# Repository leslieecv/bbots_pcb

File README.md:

# PCB Battlebots base

Este repositorio contiene las diferentes versiones de placa base, diseñadas para el curso [Battlebots](https://github.com/Battlebots-UChile) de la FCFM Uchile.
Fueron desarrolladas usando EAGLE y se complementa con el diseño

- pcbv1: utiliza Arduino UNO (funcional). Otros detalles disponibles en [Battlebot-base-testing](https://github.com/uwulises/Battlebot-base-testing).
- pcbv2: utiliza NodeMCU Amica V2 (ESP8266) y opcionalmente puede usar un Módulo Wifi ESP8266 ESP-07 (incompleta).
- pcbv3: utiliza solamente NodeMCU Amica V2 (ESP8266) (funcional). Diseño mecánico disponible en [MobileBase_ESP8266](https://github.com/uwulises/MobileBase_ESP8266).

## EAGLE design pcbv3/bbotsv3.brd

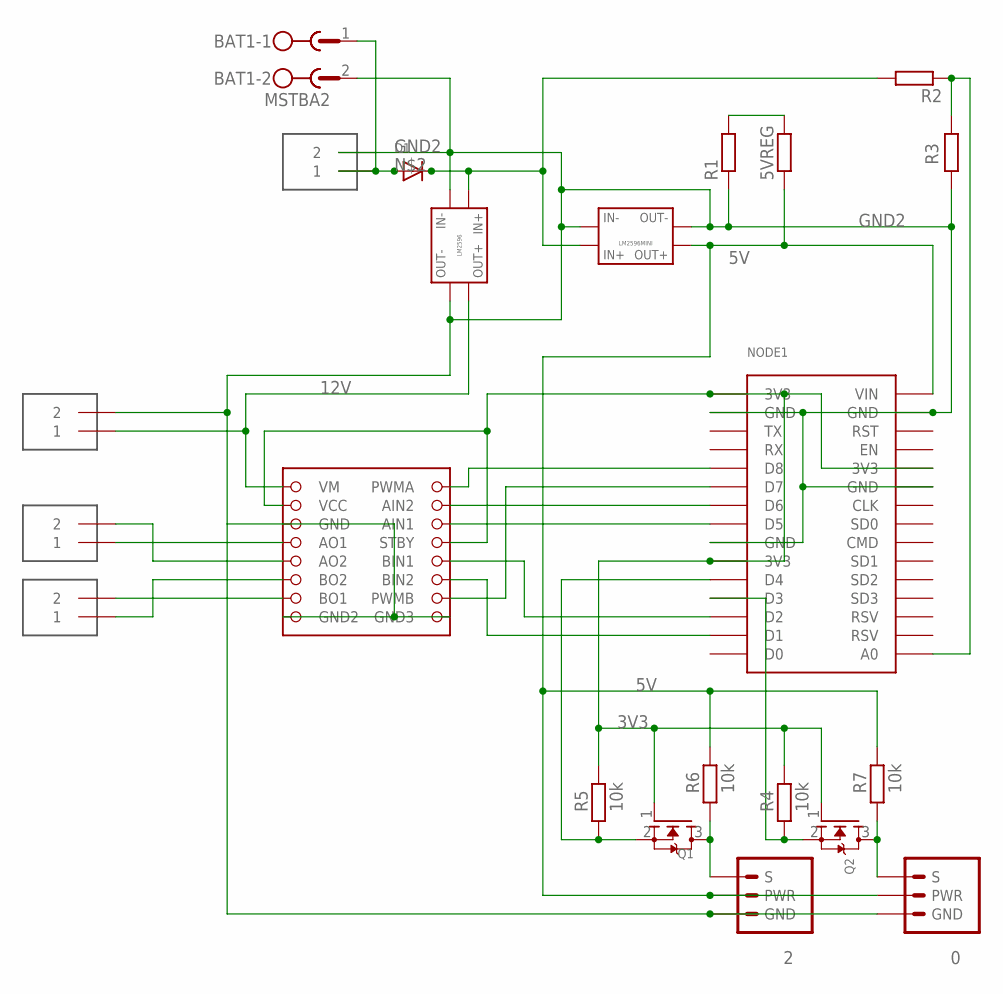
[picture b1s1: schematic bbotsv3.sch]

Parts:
0, 2: BB-PIN3BB-PIN3; 1X03
5VREG: BB-R0805; R0805
ARMA, ARMA1, ARMA2, ARMA3: TERMINAL_2P; KF301-2P
BAT1: MSTBA2
D1: DIODEDO-1N4148; DO-1N4148
NODE1: NODEMCU_ESP8266
Q1, Q2: MOSFET-NWAVE; SOT23-W
R1: 100; R1206
R2, R4, R5, R6, R7: 10k; R1206
R3: 1k; R1206
U$1: BB-LM2596
U$2: BB-TB6612
U$3: BB-LM2596MINILM2596MINIV2; LM2596MINIV2

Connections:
3V3: NODE1.3V3@1 (3V3), NODE1.3V3@2 (3V3), NODE1.3V3@3 (3V3), Q1.1 (G), Q2.1 (G), R4.2, R5.2, U$2.STBY, U$2.VCC
5V: 0.P (PWR), 2.P (PWR), 5VREG.1, NODE1.VIN, R6.2, R7.2, U$3.OUT+
11.1: D1.C, R2.2, U$1.IN+, U$3.IN+
12V: ARMA.1, U$1.OUT+, U$2.VM
GND2: 0.GND, 2.GND, ARMA.2, ARMA3.2, BAT1.2, NODE1.GND@1 (GND), NODE1.GND@2 (GND), NODE1.GND@3 (GND), NODE1.GND@4 (GND), R1.1, R3.2, U$1.IN-, U$1.OUT-, U$2.GND, U$2.GND2, U$2.GND3, U$3.IN-, U$3.OUT-
unnamed: NODE1.A0, R2.1, R3.1
unnamed: ARMA3.1, BAT1.1, D1.A
unnamed: 5VREG.2, R1.2
unnamed: NODE1.D8, U$2.PWMA
unnamed: NODE1.D7, U$2.PWMB
unnamed: ARMA2.1, U$2.BO2
unnamed: NODE1.D6, U$2.AI2 (AIN2)
unnamed: NODE1.D5, U$2.AI1 (AIN1)
unnamed: NODE1.D2, U$2.BI1 (BIN1)
unnamed: NODE1.D1, U$2.BI2 (BIN2)
unnamed: 2.S, Q1.3 (D), R6.1
unnamed: NODE1.D3, Q2.2 (S), R4.1
unnamed: ARMA1.2, U$2.AO2
unnamed: ARMA1.1, U$2.AO1
unnamed: ARMA2.2, U$2.BO1
unnamed: 0.S, Q2.3 (D), R7.1
unnamed: NODE1.D4, Q1.2 (S), R5.1

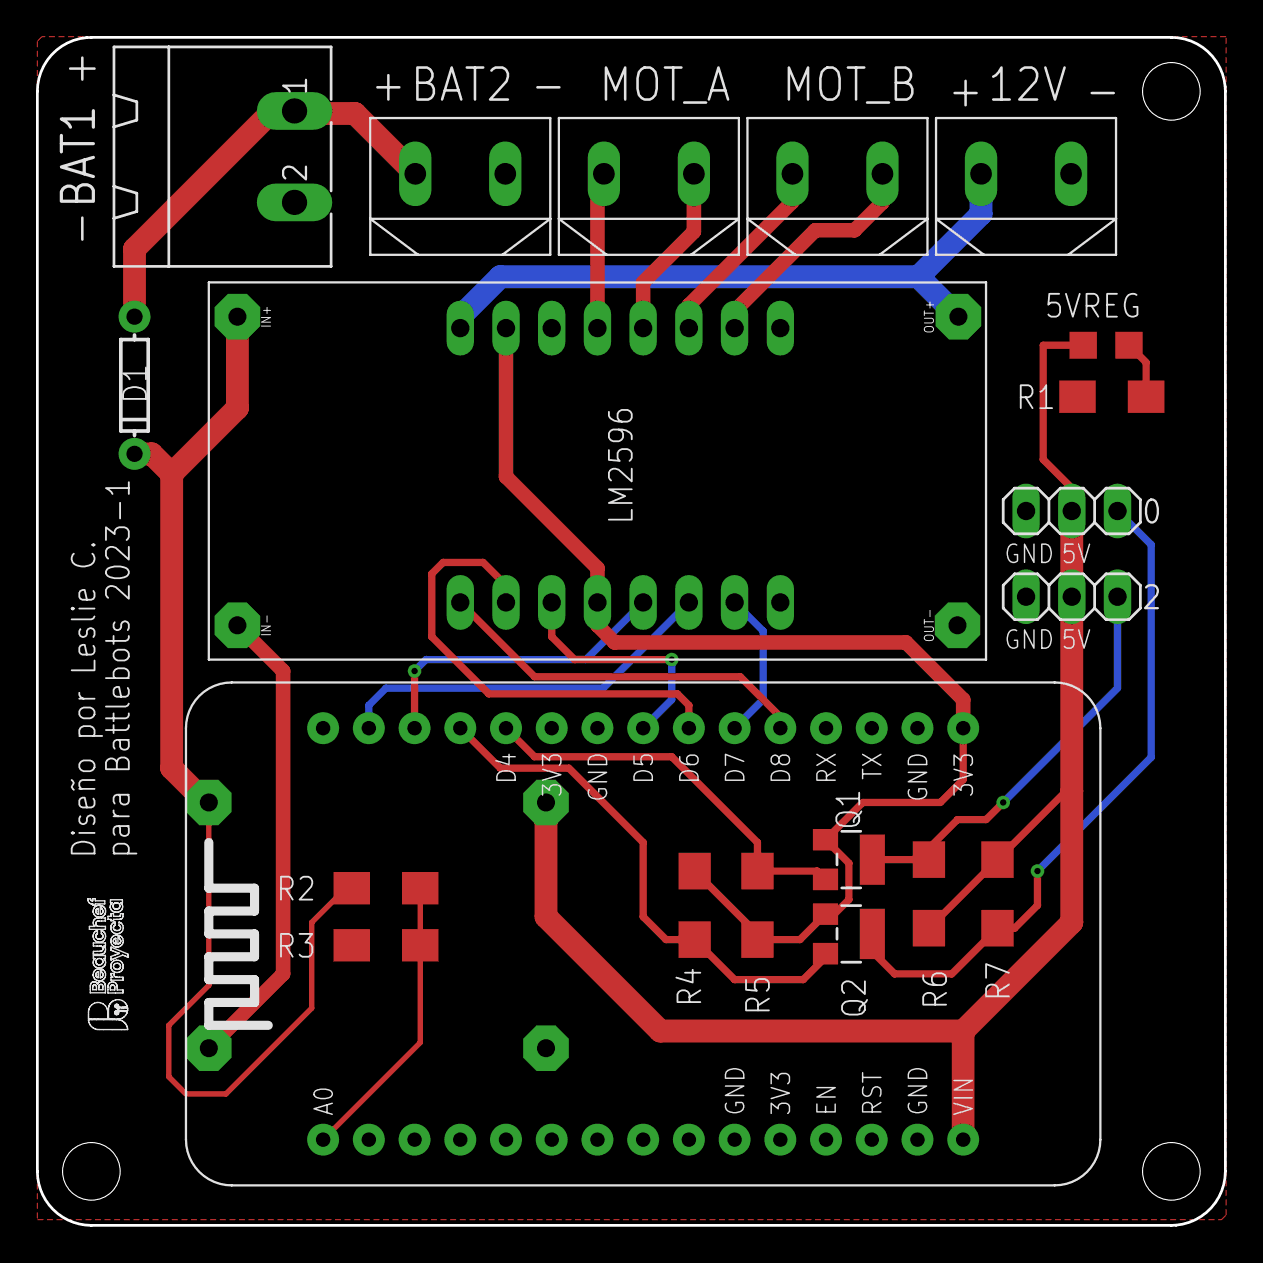
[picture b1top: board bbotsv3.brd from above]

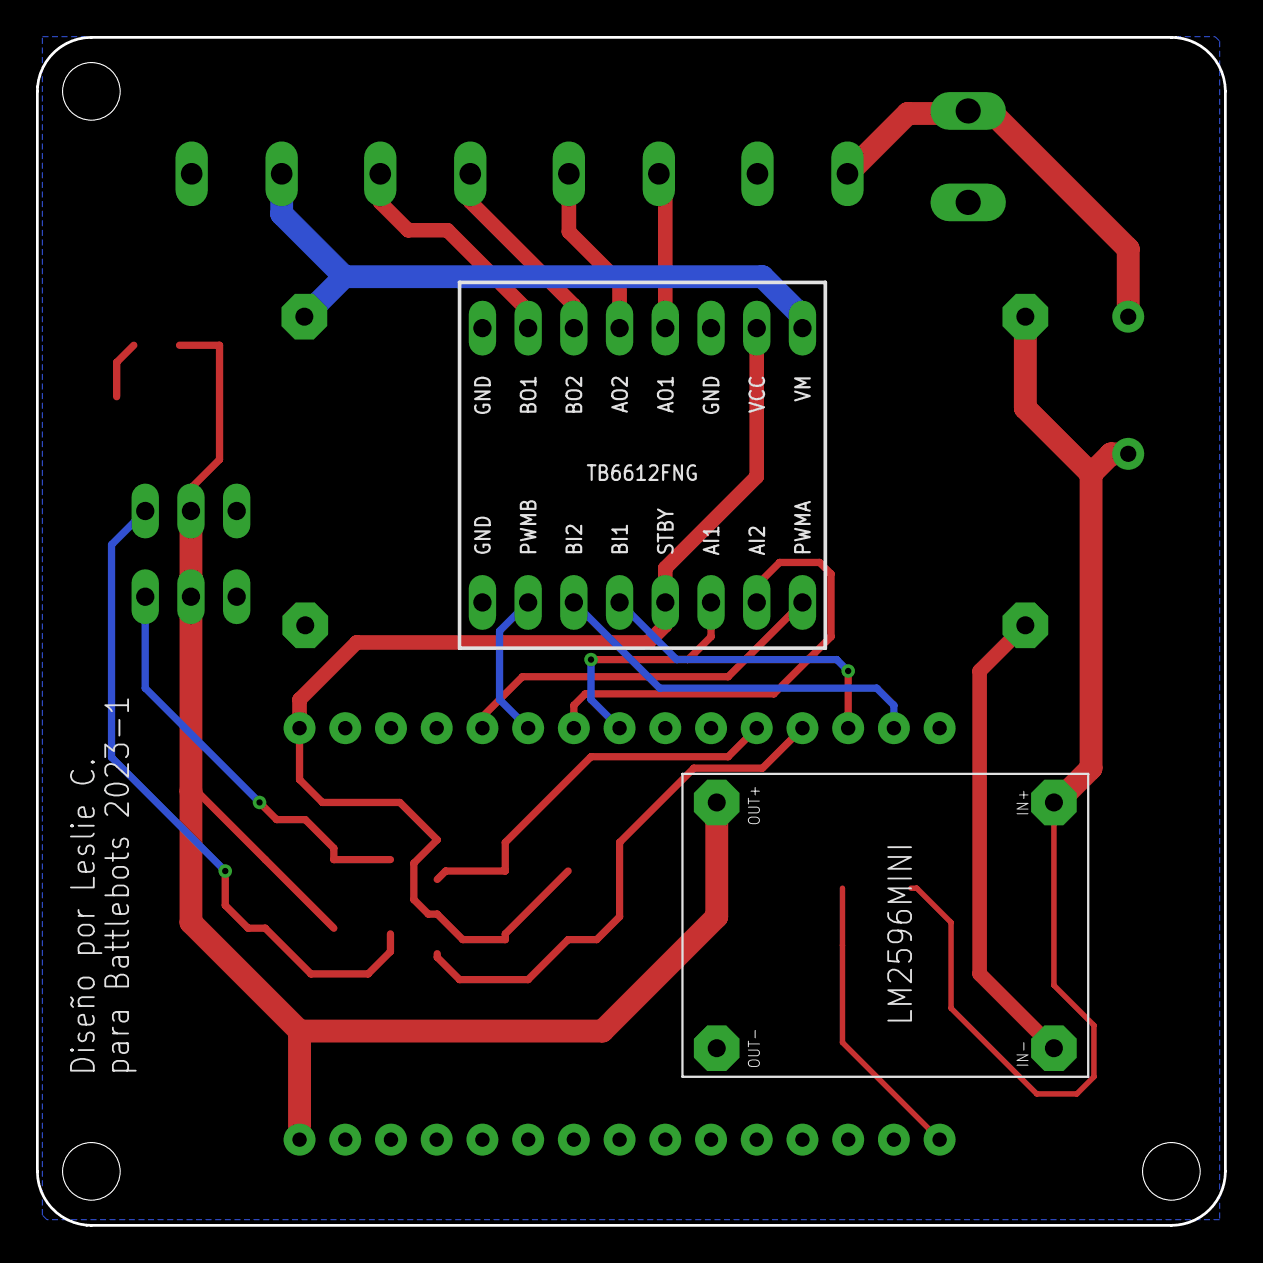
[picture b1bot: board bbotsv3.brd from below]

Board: 2 copper layers, 66.0 x 66.0 mm, 22 parts (2 on the bottom side), 22 nets.

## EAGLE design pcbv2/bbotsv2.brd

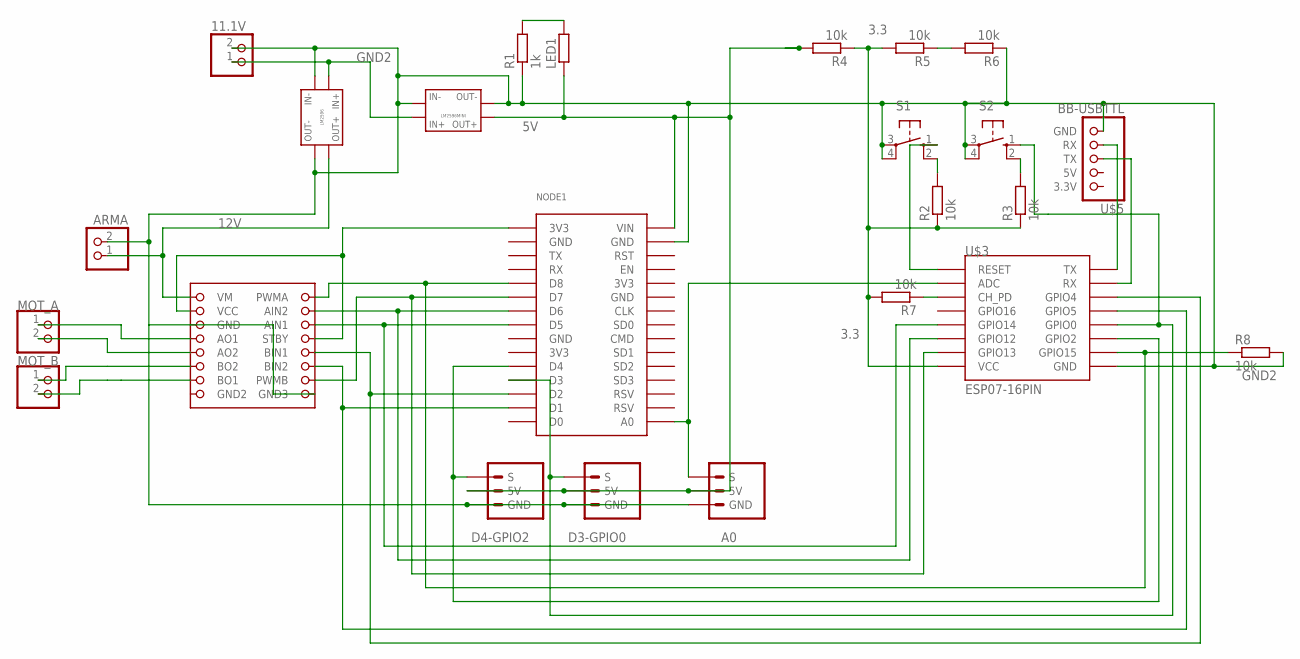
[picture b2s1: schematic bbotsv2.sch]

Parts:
11.1V: JST_2PIN-THM; JST-PH-2-THM
A0: BB-PIN3
ARMA: JST_2PIN-THM; JST-PH-2-THM
D3-GPIO0, D4-GPIO2: BB-PIN3
LED1: BB-RESM0805; M0805
MOT_A: JST_2PIN-THM; JST-PH-2-THM
MOT_B: JST_2PIN-THM; JST-PH-2-THM
NODE1: NODEMCU_ESP8266
R1: 1k; M0805
R2, R3, R4, R5, R6, R7, R8: 10k; M0805
S1, S2: 10-XX; B3F-10XX
U$1: BB-LM2596
U$2: BB-TB6612
U$3: ESP07-16PIN
U$4: BB-LM2596MINI
U$5: BB-USBTTL; 1X05

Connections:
3.3: R2.1, R3.1, R4.1, R5.2, R7.2, U$3.VCC
3V3: NODE1.3V3@2 (3V3), NODE1.3V3@3 (3V3)
5V: A0.2 (5V), D3-GPIO0.2 (5V), D4-GPIO2.2 (5V), LED1.1, NODE1.VIN, R4.2, U$4.OUT+
11.1: 11.1V.1 (2), U$1.IN+, U$4.IN+
12V: ARMA.1 (2), U$1.OUT+, U$2.VM
GND: NODE1.GND@1 (GND), NODE1.GND@2 (GND), NODE1.GND@3 (GND)
GND2: 11.1V.2 (1), A0.1 (GND), ARMA.2 (1), D3-GPIO0.1 (GND), D4-GPIO2.1 (GND), NODE1.GND@4 (GND), R1.1, R6.1, R8.2, S1.3, S1.4 (P1), S2.3, S2.4 (P1), U$1.IN-, U$1.OUT-, U$2.GND, U$2.GND3, U$3.GND, U$4.IN-, U$4.OUT-, U$5.GND; also elsewhere on the board
unnamed: LED1.2, R1.2
unnamed: NODE1.D8, R8.1, U$2.PWMA, U$3.GPIO15
unnamed: NODE1.D7, U$2.PWMB, U$3.GPIO13
unnamed: NODE1.D6, U$2.AI2 (AIN2), U$3.GPIO12
unnamed: NODE1.D5, U$2.AI1 (AIN1), U$3.GPIO14
unnamed: NODE1.D2, U$2.BI1 (BIN1), U$3.GPIO4
unnamed: NODE1.D1, U$2.BI2 (BIN2), U$3.GPIO5
unnamed: D4-GPIO2.3 (S), NODE1.D4, U$3.GPIO2
unnamed: MOT_A.2 (1), U$2.AO2
unnamed: MOT_A.1 (2), U$2.AO1
unnamed: MOT_B.1 (2), U$2.BO2
unnamed: MOT_B.2 (1), U$2.BO1
unnamed: NODE1.3V3@1 (3V3), U$2.STBY, U$2.VCC
unnamed 20: D3-GPIO0.3 (S), NODE1.D3, S2.1 (S), U$3.GPIO0; also elsewhere on the board
unnamed: U$3.TX, U$5.RX
unnamed: U$3.RX, U$5.TX
unnamed: A0.3 (S), NODE1.A0, U$3.ADC
unnamed 24: R2.2, S1.2 (S1); also elsewhere on the board
unnamed 25: R3.2, S2.2 (S1); also elsewhere on the board
unnamed: R5.1, R6.2
unnamed 27: S1.1 (S), U$3.REST (RESET); also elsewhere on the board
unnamed: R7.1, U$3.CH_PD

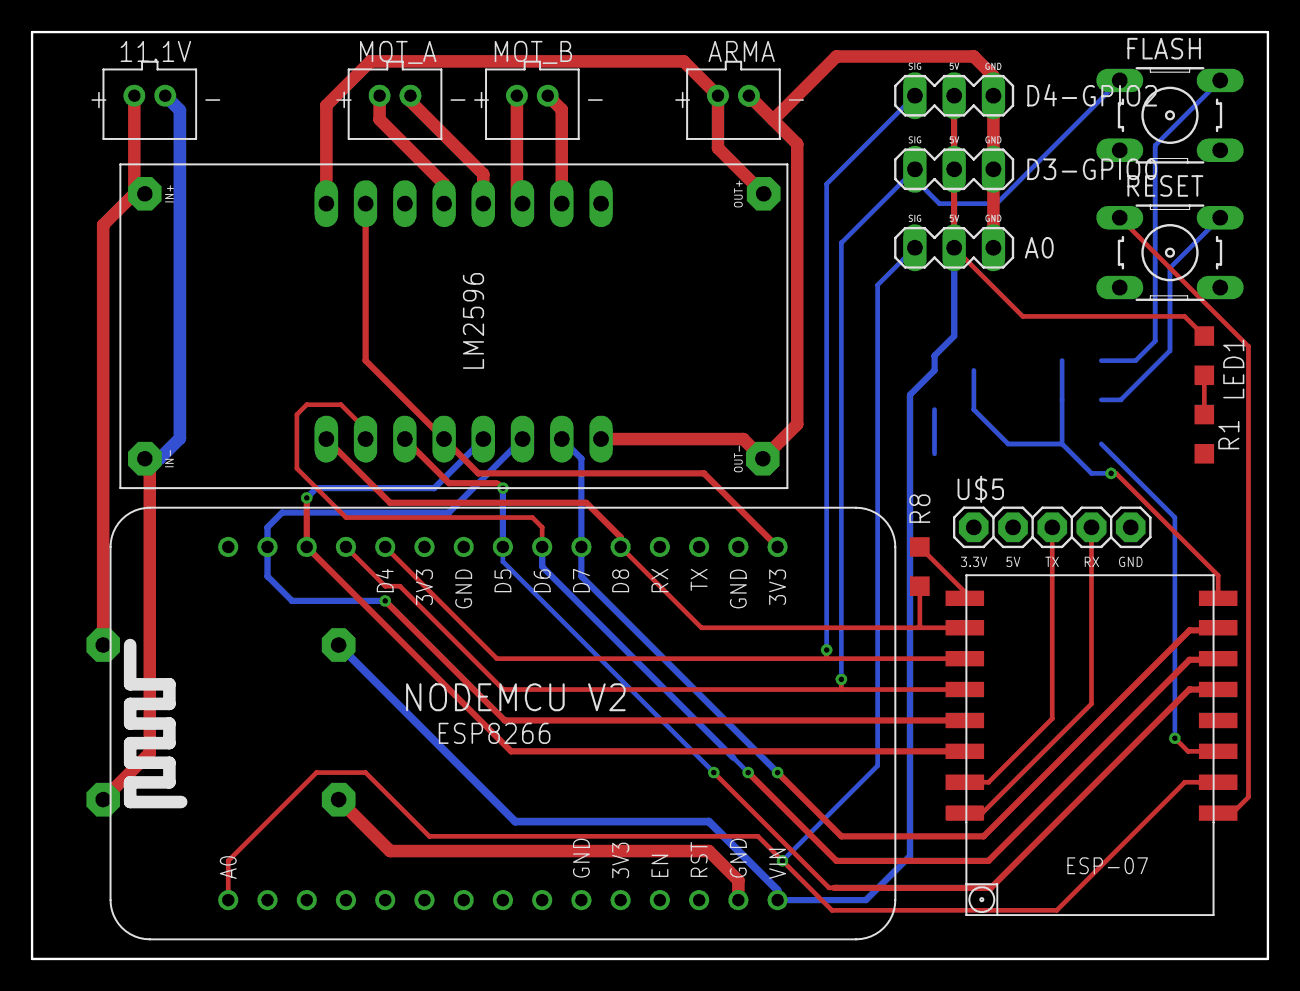
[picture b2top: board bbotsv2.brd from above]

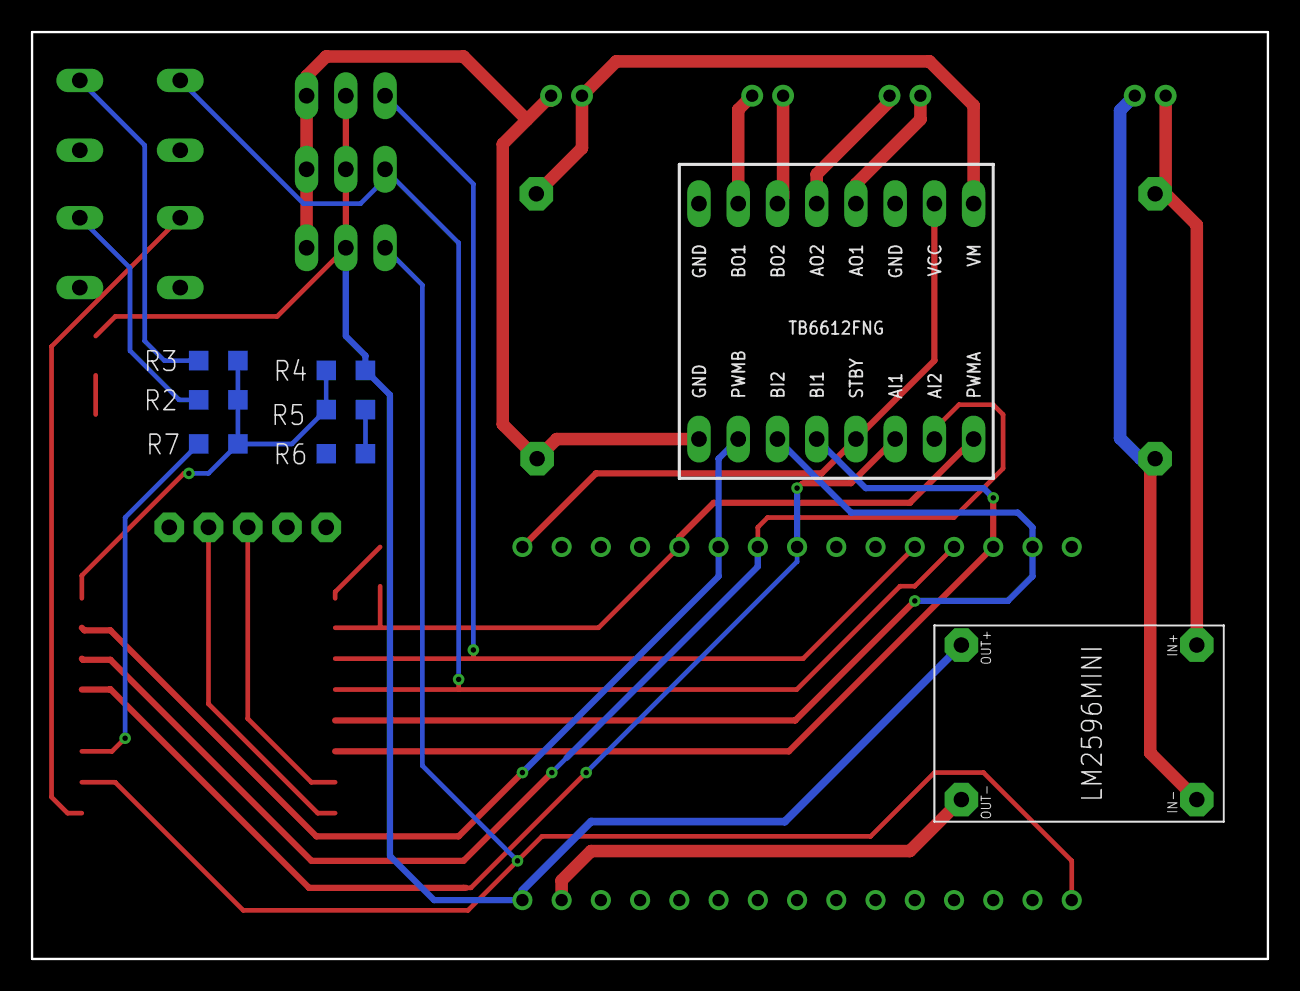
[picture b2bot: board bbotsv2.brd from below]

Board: 2 copper layers, 80.0 x 60.0 mm, 24 parts (8 on the bottom side), 29 nets.

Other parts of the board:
FLASH: B3F-10XX
RESET: B3F-10XX

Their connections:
GND2: FLASH.3, FLASH.4, RESET.3, RESET.4; also elsewhere on the board
unnamed 20: FLASH.1; also elsewhere on the board
unnamed 24: RESET.2; also elsewhere on the board
unnamed 25: FLASH.2; also elsewhere on the board
unnamed 27: RESET.1; also elsewhere on the board

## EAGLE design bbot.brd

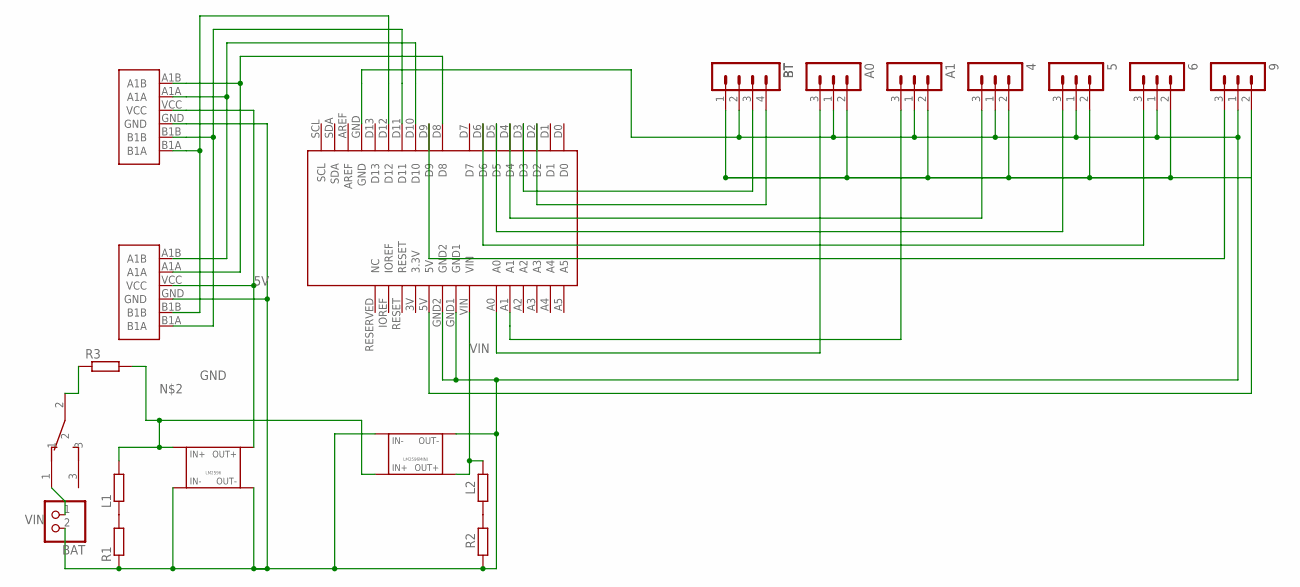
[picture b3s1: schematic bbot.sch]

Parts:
4, 5, 6, 9: BB-PIN3
A0, A1: BB-PIN3
BAT: VIN; JST-PH-2-THM
BT: BB-HC06
L1, L2: BB-RESM0805; M0805
LM2596: BB-LM2596
LM2596MINI: BB-LM2596MINI
R1, R2: BB-RESM0805; M0805
R3: R-EU_0207/5V; 0207/5V
SW1: BB-SWITCHBB-SW; BB-SWITCH
U$1: BB-ARD
U$2, U$3: BB-PTEH

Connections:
5V: LM2596.OUT+, U$2.VCC, U$3.VCC
5V-A: 4.2 (5V), 5.2 (5V), 6.2 (5V), 9.2 (5V), A0.2 (5V), A1.2 (5V), BT.1, U$1.5V
7.4V: L1.2, LM2596.IN+, LM2596MINI.IN+, R3.2
GND: 4.1 (GND), 5.1 (GND), 6.1 (GND), 9.1 (GND), A0.1 (GND), A1.1 (GND), BAT.2 (1), BT.2, LM2596.IN-, LM2596.OUT-, LM2596MINI.IN-, LM2596MINI.OUT-, R1.1, R2.1, U$1.GND, U$1.GND1, U$1.GND2, U$2.GND, U$3.GND
unnamed: BT.3, U$1.D3
unnamed: R3.1, SW1.2
unnamed: L1.1, R1.2
unnamed: 9.3 (S), U$1.D9
unnamed: BAT.1 (2), SW1.1
unnamed: U$1.D11, U$2.B1B, U$3.B1A
unnamed: BT.4, U$1.D2
unnamed: U$1.D12, U$2.B1A, U$3.B1B
unnamed: U$1.D10, U$2.A1A, U$3.A1B
unnamed: U$1.D8, U$2.A1B, U$3.A1A
unnamed: 6.3 (S), U$1.D6
unnamed: 5.3 (S), U$1.D5
unnamed: 4.3 (S), U$1.D4
unnamed: A1.3 (S), U$1.A1
unnamed: A0.3 (S), U$1.A0
unnamed: L2.1, R2.2
VIN: L2.2, LM2596MINI.OUT+, U$1.VIN

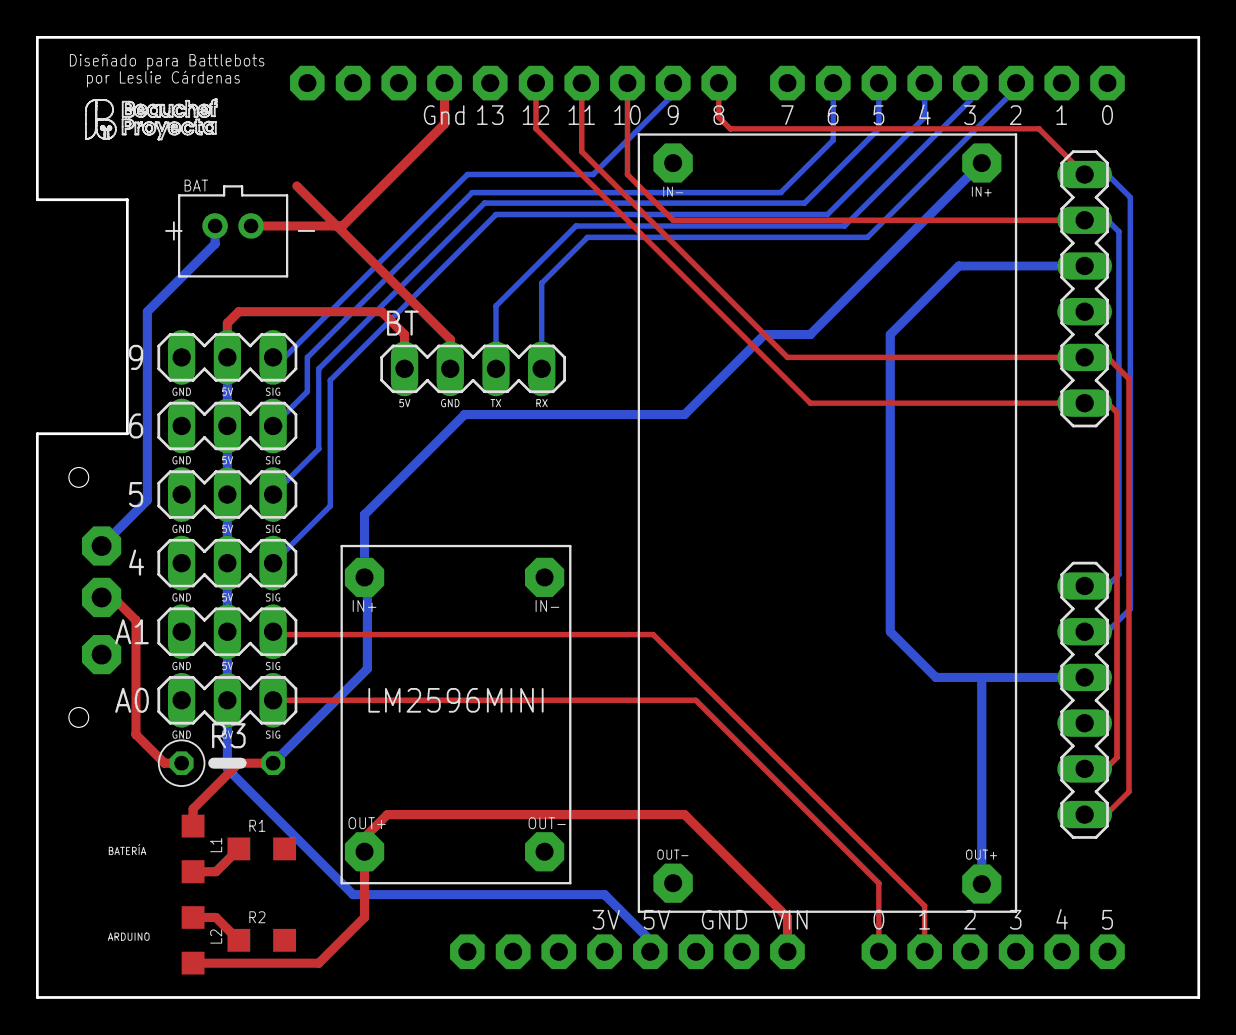
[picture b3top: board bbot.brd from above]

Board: 2 copper layers, 64.5 x 53.3 mm, 19 parts (0 on the bottom side), 21 nets.

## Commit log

2022-09-20 added new files
2022-09-20 added lm2596, everything is working
2022-09-21 added some tags to brd
2022-09-26 changed footprint arduino and h bridge, and added more tags
2022-10-11 added bp label and diode
2022-10-16 added bp logo, ready to manufacture
2022-11-23 added document with instructions for connecting components and setting pins
2023-02-06 started pcb v2 2023
2023-03-12 connected everything to amica, not tested
2023-03-13 connected esp07 on schematic and ruted all components
2023-03-23 changed version of lm2596mini
2023-03-28 added connections for voltage tester
2023-03-31 finish pcb, waiting review
2023-04-03 ready to manufacture, review done
2023-04-12 last update of pcbv3, add gerber/zip file for manufacture
2023-05-08 Update README.md
    update status on README
2023-10-29 add pcb images
